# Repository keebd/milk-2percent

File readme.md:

# 2% Milk keyboard

### [Build Guide](https://spaceboards.xyz/hardware/2milkbuild)

### Credits
- Case made by Soft
- PCB made by PyroL

### Updates
- 9/8/22 [KEEBD] Update RGB strip pins so GND is square.
- 1/27/21 WRONG LINK TO BUILD GUIDE.  UPDATED WITH CORRECT LINK.
- 8/22/19 WRONG FILE WAS UPLOADED EARLIER. USB PORT PLACEMENT WAS INCORRECT. CORRECT FILE HAS BEEN UPLOADED.

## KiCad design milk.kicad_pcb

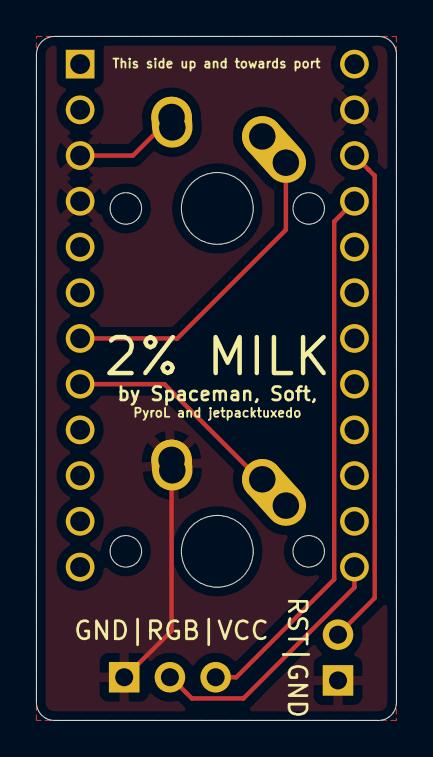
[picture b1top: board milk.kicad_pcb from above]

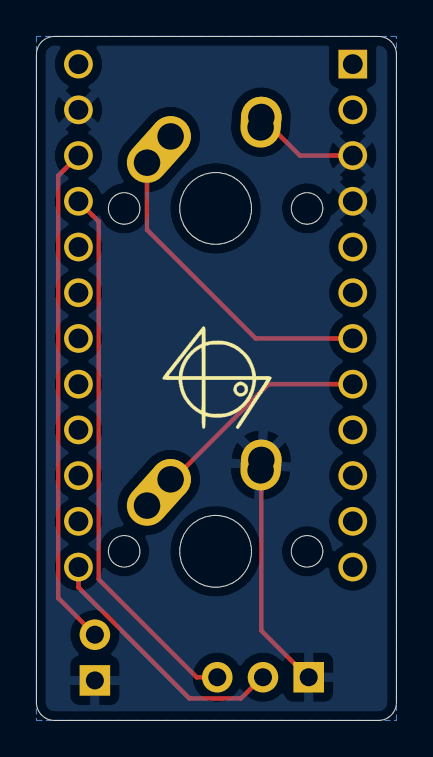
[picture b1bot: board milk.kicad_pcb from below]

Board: 2 copper layers, 20.0 x 38.0 mm, 5 parts (2 on the bottom side), 6 nets.

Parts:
J1: RGB; PinHeader_1x03_P2.54mm_Vertical
J4: RST; PinHeader_1x02_P2.54mm_Vertical
K1, K2: KEYSW; MX-1U-NoLED
U1: ProMicro; ProMicro_NoSilk

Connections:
/RGB: J1.2, U1.13 (B6)
/RST: J4.2, U1.22 (RST)
/k1: K1.1 (COL), U1.7 (D4)
/k2: K2.1 (COL), U1.8 (C6)
GND: J1.1, J4.1, K2.2 (ROW), U1.3 (GND), U1.4 (GND), U1.23 (GND)
VCC: J1.3, U1.21 (VCC)

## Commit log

2022-09-07 Updated to include libraries and footprints localy as well as fixed the RGB strip pins orientation
2022-09-07 Update readme with recent change
2022-09-08 Remove old files
2022-09-08 Add JLCPCB Fab Files
